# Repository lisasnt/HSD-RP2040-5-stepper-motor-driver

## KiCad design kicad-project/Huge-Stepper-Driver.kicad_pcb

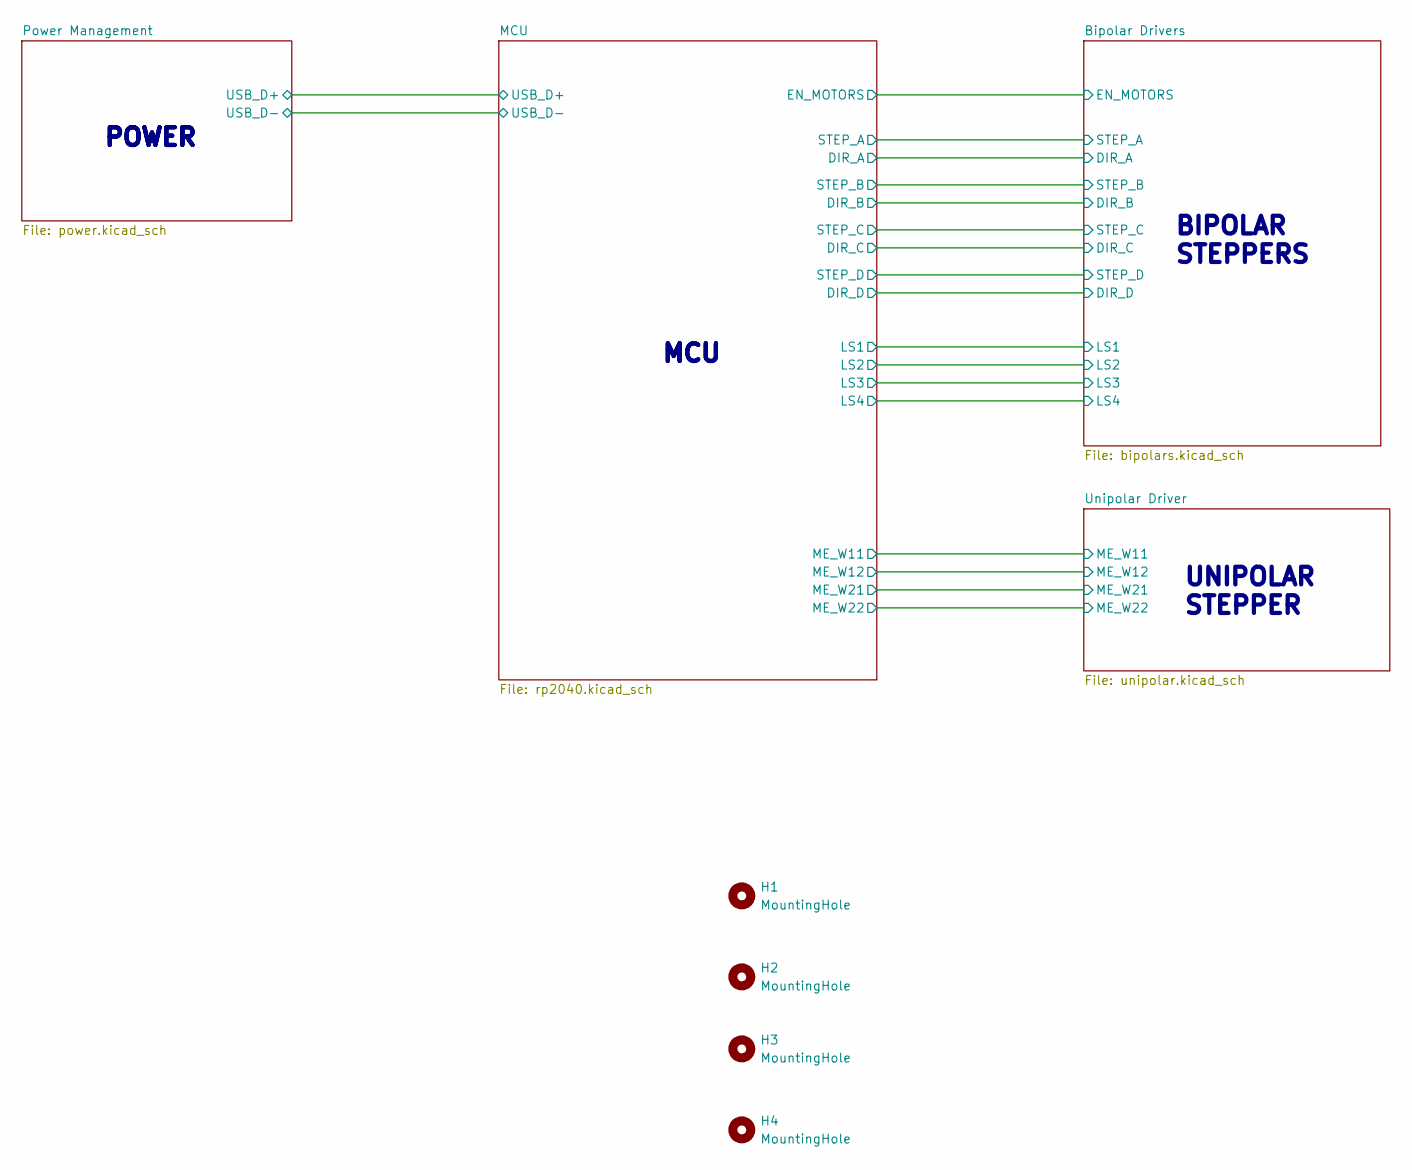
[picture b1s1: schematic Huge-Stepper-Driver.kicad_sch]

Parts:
H1, H2, H3, H4: MountingHole; MountingHole_3.2mm_M3

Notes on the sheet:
MCU
UNIPOLAR STEPPER
POWER
BIPOLAR STEPPERS

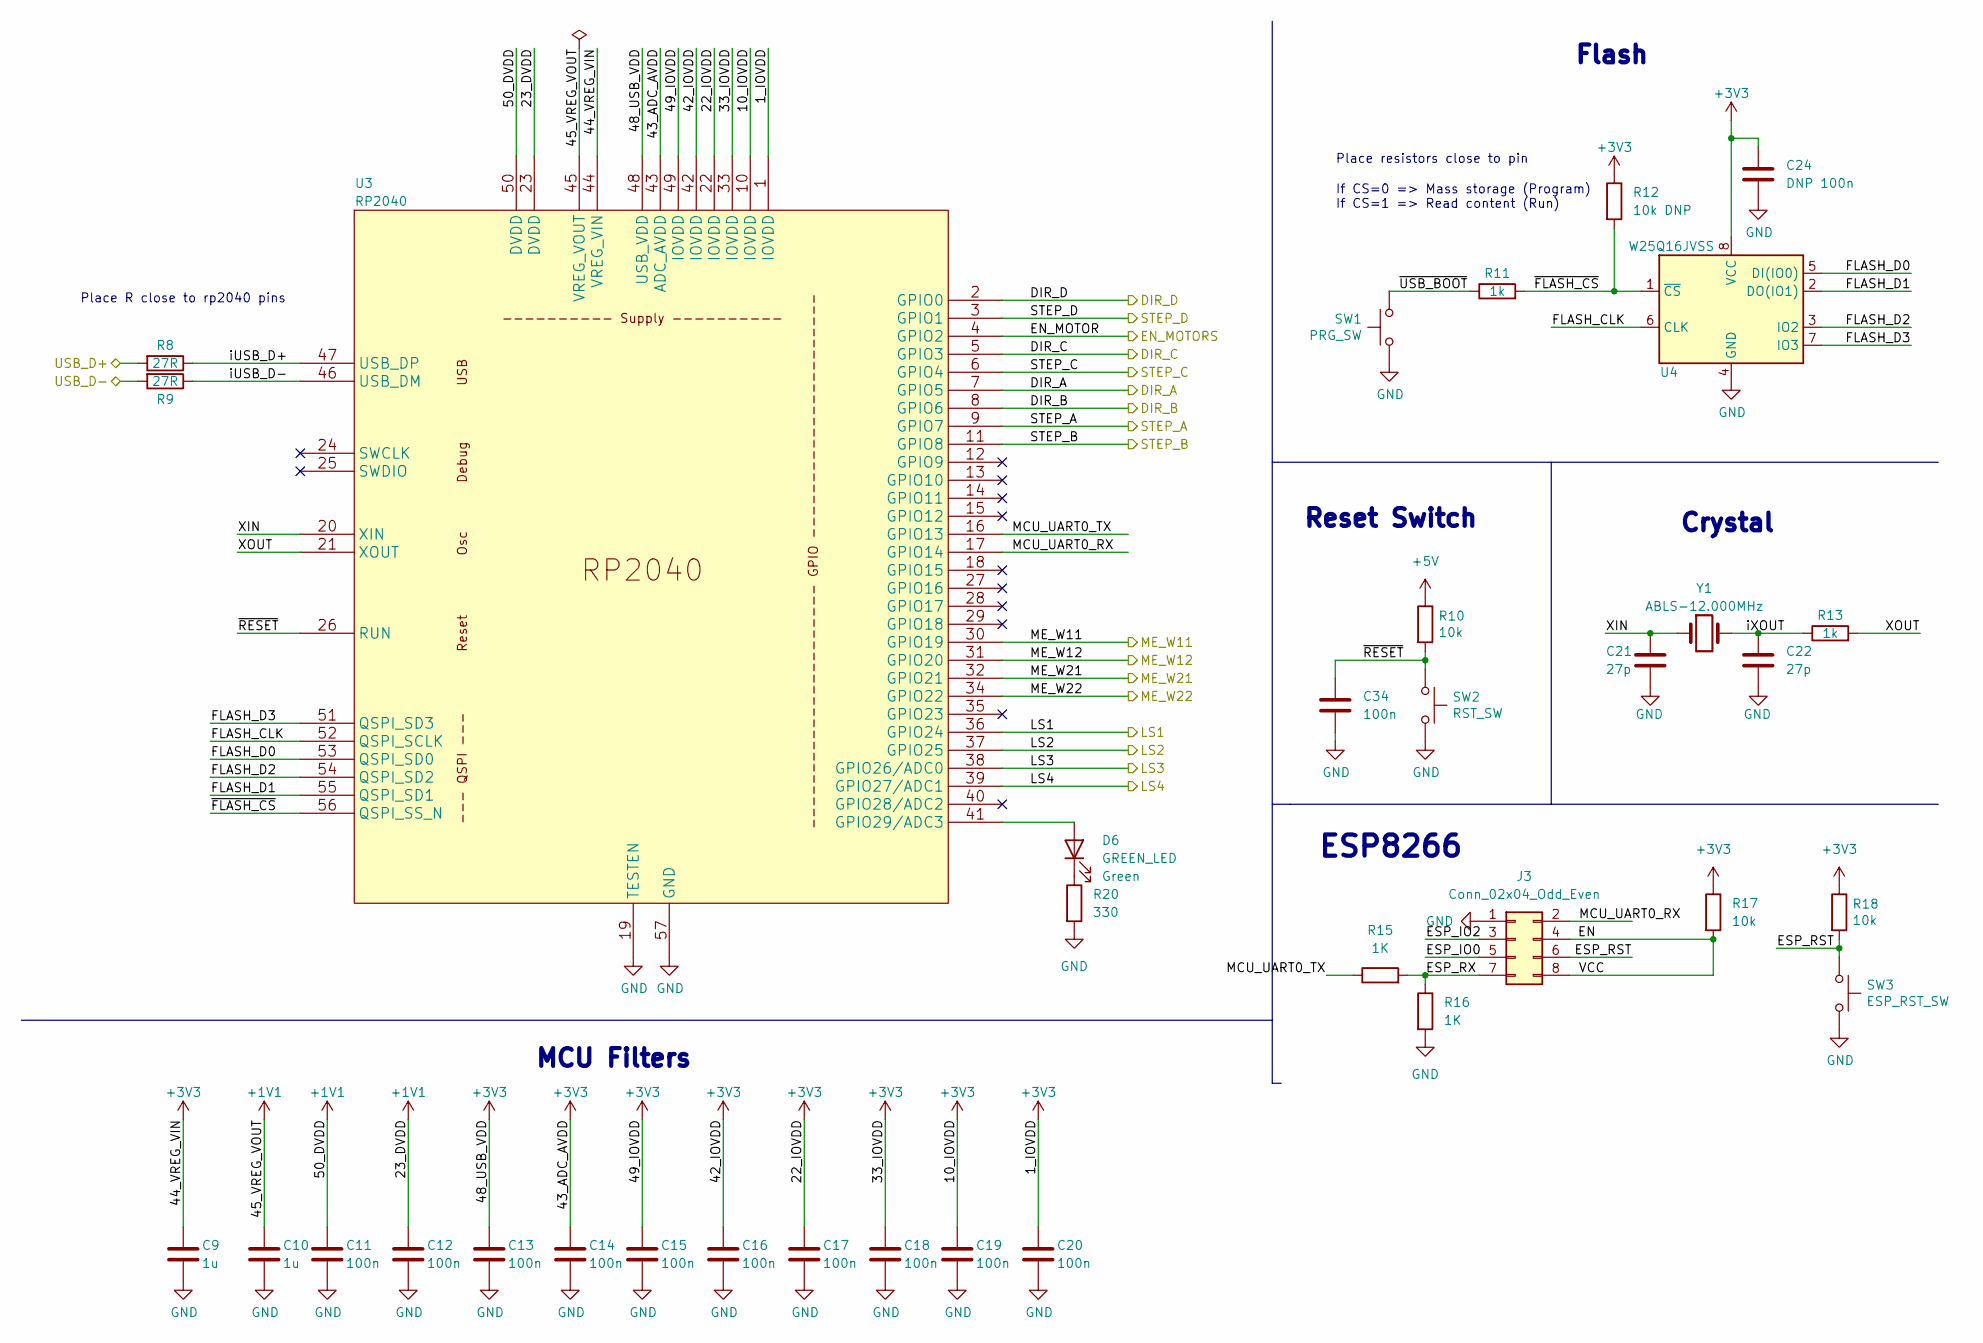
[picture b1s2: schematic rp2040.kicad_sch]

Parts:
C9, C10: 1u; C_0805_2012Metric
C11, C12, C13, C14, C15, C16, C17, C18, C19, C20, C34: 100n; C_0603_1608Metric
C21, C22: 27p; C_0603_1608Metric
C24: DNP 100n; C_0603_1608Metric
D6: GREEN_LED; LED_0603_1608Metric
J3: Conn_02x04_Odd_Even; PinHeader_2x04_P2.54mm_Vertical
R8, R9: 27R; R_0603_1608Metric
R10, R17, R18: 10k; R_0603_1608Metric
R11, R13: 1k; R_0603_1608Metric
R12: 10k DNP; R_0603_1608Metric
R15, R16: 1K; R_0603_1608Metric
R20: 330; R_0603_1608Metric
SW1: PRG_SW; SW_Push_1P1T_NO_CK_KMR2
SW2: RST_SW; SW_Push_1P1T_NO_CK_KMR2
SW3: ESP_RST_SW; SW_Push_1P1T_NO_CK_KMR2
U3: RP2040; RP2040-Hand-Solder
U4: W25Q16JVSS; SOIC-8_5.23x5.23mm_P1.27mm
Y1: ABLS-12.000MHz; Crystal_SMD_HC49-SD

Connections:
+1V1: C10.1, C11.1, C12.1, U3.23 (DVDD), U3.45 (VREG_VOUT), U3.50 (DVDD)
+5V: R10.1; also elsewhere on the board
/Bipolar Drivers/LS1: U3.36 (GPIO24); also elsewhere on the board
/Bipolar Drivers/LS2: U3.37 (GPIO25); also elsewhere on the board
/Bipolar Drivers/LS3: U3.38 (GPIO26/ADC0); also elsewhere on the board
/Bipolar Drivers/LS4: U3.39 (GPIO27/ADC1); also elsewhere on the board
/MCU/DIR_A: U3.7 (GPIO5); also elsewhere on the board
/MCU/DIR_B: U3.8 (GPIO6); also elsewhere on the board
/MCU/DIR_C: U3.5 (GPIO3); also elsewhere on the board
/MCU/DIR_D: U3.2 (GPIO0); also elsewhere on the board
/MCU/EN: J3.4, J3.8, R17.2
/MCU/EN_MOTOR: U3.4 (GPIO2); also elsewhere on the board
/MCU/ESP_IO0: J3.5
/MCU/ESP_IO2: J3.3
/MCU/ESP_RST: J3.6, R18.2, SW3.1
/MCU/ESP_RX: J3.7, R15.2, R16.1
/MCU/FLASH_CLK: U3.52 (QSPI_SCLK), U4.6 (CLK)
/MCU/FLASH_D0: U3.53 (QSPI_SD0), U4.5 (DI(IO0))
/MCU/FLASH_D1: U3.55 (QSPI_SD1), U4.2 (DO(IO1))
/MCU/FLASH_D2: U3.54 (QSPI_SD2), U4.3 (IO2)
/MCU/FLASH_D3: U3.51 (QSPI_SD3), U4.7 (IO3)
/MCU/MCU_UART0_RX: J3.2, U3.17 (GPIO14)
/MCU/MCU_UART0_TX: R15.1, U3.16 (GPIO13)
/MCU/ME_W11: U3.30 (GPIO19); also elsewhere on the board
/MCU/ME_W12: U3.31 (GPIO20); also elsewhere on the board
/MCU/ME_W21: U3.32 (GPIO21); also elsewhere on the board
/MCU/ME_W22: U3.34 (GPIO22); also elsewhere on the board
/MCU/STEP_A: U3.9 (GPIO7); also elsewhere on the board
/MCU/STEP_B: U3.11 (GPIO8); also elsewhere on the board
/MCU/STEP_C: U3.6 (GPIO4); also elsewhere on the board
/MCU/STEP_D: U3.3 (GPIO1); also elsewhere on the board
/MCU/USB_D+: R8.2; also elsewhere on the board
/MCU/USB_D-: R9.2; also elsewhere on the board
/MCU/XIN: C21.1, U3.20 (XIN), Y1.1
/MCU/XOUT: R13.2, U3.21 (XOUT)
/MCU/iUSB_D+: R8.1, U3.47 (USB_DP)
/MCU/iUSB_D-: R9.1, U3.46 (USB_DM)
/MCU/iXOUT: C22.1, R13.1, Y1.2
/MCU/~FLASH_CS: R11.2, R12.2, U3.56 (QSPI_SS_N), U4.1 (~CS)
/MCU/~RESET: C34.1, R10.2, SW2.1, U3.26 (RUN)
/MCU/~USB_BOOT: R11.1, SW1.1
GND: C9.2, C10.2, C11.2, C12.2, C13.2, C14.2, C15.2, C16.2, C17.2, C18.2, C19.2, C20.2, C21.2, C22.2, C24.2, C34.2, J3.1, R16.2, R20.2, SW1.2, SW2.2, SW3.2, U3.19 (TESTEN), U3.57 (GND), U4.4 (GND); also elsewhere on the board
unnamed: D6.1 (K), R20.1
unnamed: D6.2 (A), U3.41 (GPIO29/ADC3)

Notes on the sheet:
Reset Switch
Crystal
ESP8266
Flash
If CS=0 => Mass storage (Program) If CS=1 => Read content (Run)
Place resistors close to pin
MCU Filters
Place R close to rp2040 pins

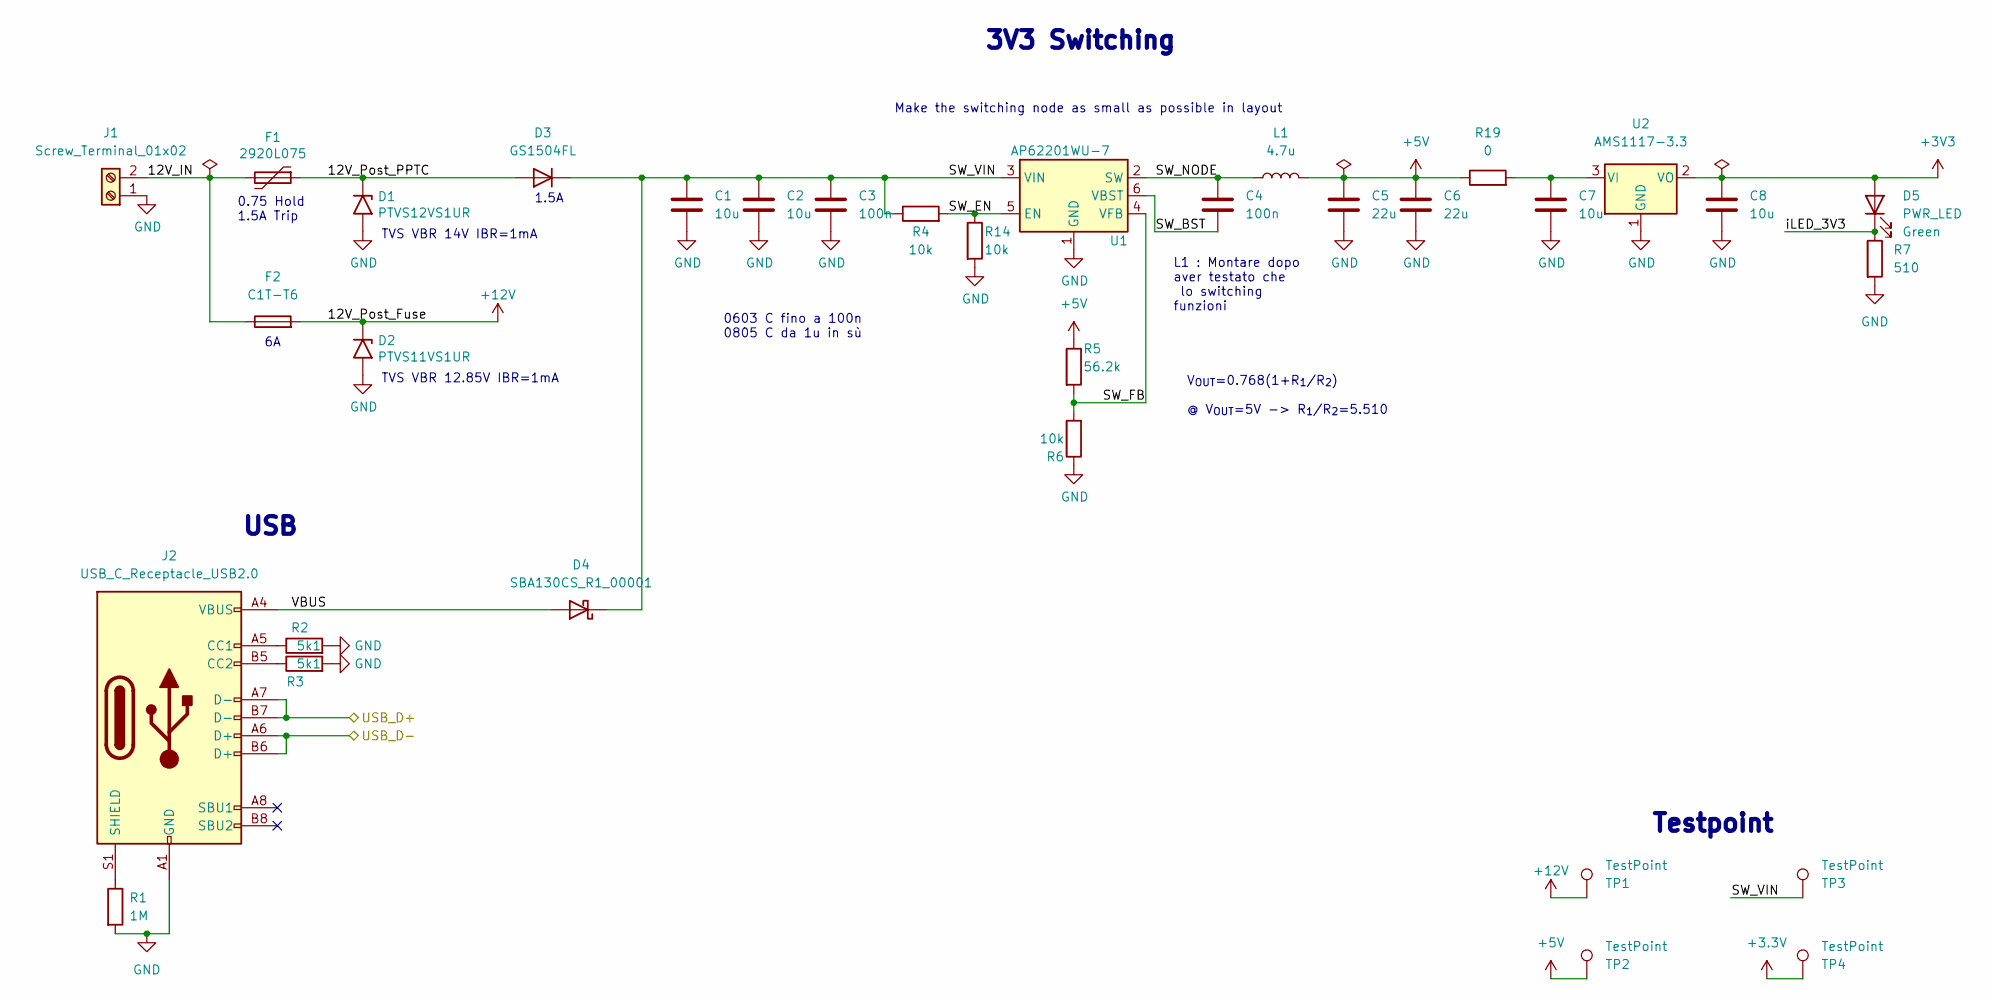
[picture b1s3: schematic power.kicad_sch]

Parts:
C1, C2, C7, C8: 10u; C_0805_2012Metric
C3, C4: 100n; C_0603_1608Metric
C5, C6: 22u; C_0805_2012Metric
D1: PTVS12VS1UR; D_SOD-123
D2: PTVS11VS1UR; D_SOD-123
D3: GS1504FL; D_SOD-123F
D4: SBA130CS_R1_00001; D_SOD-323
D5: PWR_LED; LED_0603_1608Metric
F1: 2920L075; Fuse_2920_7451Metric
F2: C1T-T6; Fuse_1206_3216Metric
J1: Screw_Terminal_01x02; TerminalBlock_RND_205-00001_1x02_P5.00mm_Horizontal
J2: USB_C_Receptacle_USB2.0; USB-C-USB4105-GF-A-120
L1: 4.7u; Inductance
R1: 1M; R_0603_1608Metric
R2, R3: 5k1; R_0603_1608Metric
R4, R6, R14: 10k; R_0603_1608Metric
R5: 56.2k; R_0603_1608Metric
R7: 510; R_0603_1608Metric
R19: 0; R_0603_1608Metric
TP1, TP2, TP3, TP4: TestPoint; TestPoint_Keystone_5005-5009_Compact
U1: AP62201WU-7; TSOT-23-6
U2: AMS1117-3.3; SOT-223-3_TabPin2

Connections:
+5V: C5.1, C6.1, L1.2, R5.1, R19.1, TP2.1; also elsewhere on the board
+12V: D2.1 (A1), F2.2, TP1.1; also elsewhere on the board
/MCU/USB_D+: J2.A7 (D-), J2.B7 (D-); also elsewhere on the board
/MCU/USB_D-: J2.A6 (D+), J2.B6 (D+); also elsewhere on the board
/Power Management/12V_IN: F1.2, F2.1, J1.2
/Power Management/12V_Post_PPTC: D1.1 (A1), D3.2 (A), F1.1
/Power Management/SW_BST: C4.2, U1.6 (VBST)
/Power Management/SW_EN: R4.2, R14.1, U1.5 (EN)
/Power Management/SW_FB: R5.2, R6.2, U1.4 (VFB)
/Power Management/SW_NODE: C4.1, L1.1, U1.2 (SW)
/Power Management/SW_VIN: C1.1, C2.1, C3.1, D3.1 (K), D4.1 (K), R4.1, TP3.1, U1.3 (VIN)
/Power Management/VBUS: D4.2 (A), J2.A4 (VBUS), J2.A9 (VBUS), J2.B4 (VBUS), J2.B9 (VBUS)
/Power Management/iLED_3V3: D5.1 (K), R7.1
GND: C1.2, C2.2, C3.2, C5.2, C6.2, C7.2, C8.2, D1.2 (A2), D2.2 (A2), J1.1, J2.A1 (GND), J2.A12 (GND), J2.B1 (GND), J2.B12 (GND), R1.2, R2.2, R3.2, R6.1, R7.2, R14.2, U1.1 (GND), U2.1 (GND); also elsewhere on the board
unnamed: C7.1, R19.2, U2.3 (VI)
unnamed: J2.A5 (CC1), R2.1
unnamed: J2.B5 (CC2), R3.1
unnamed: J2.S1 (SHIELD), R1.1

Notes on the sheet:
L1 : Montare dopo aver testato che lo switching funzioni
TVS VBR 14V IBR=1mA
Make the switching node as small as possible in layout
Testpoint
0603 C fino a 100n 0805 C da 1u in sù
1.5A
V_{OUT}=0.768(1+R_{1}/R_{2}) @ V_{OUT}=5V -> R_{1}/R_{2}=5.510
0.75 Hold 1.5A Trip
USB
TVS VBR 12.85V IBR=1mA
3V3 Switching

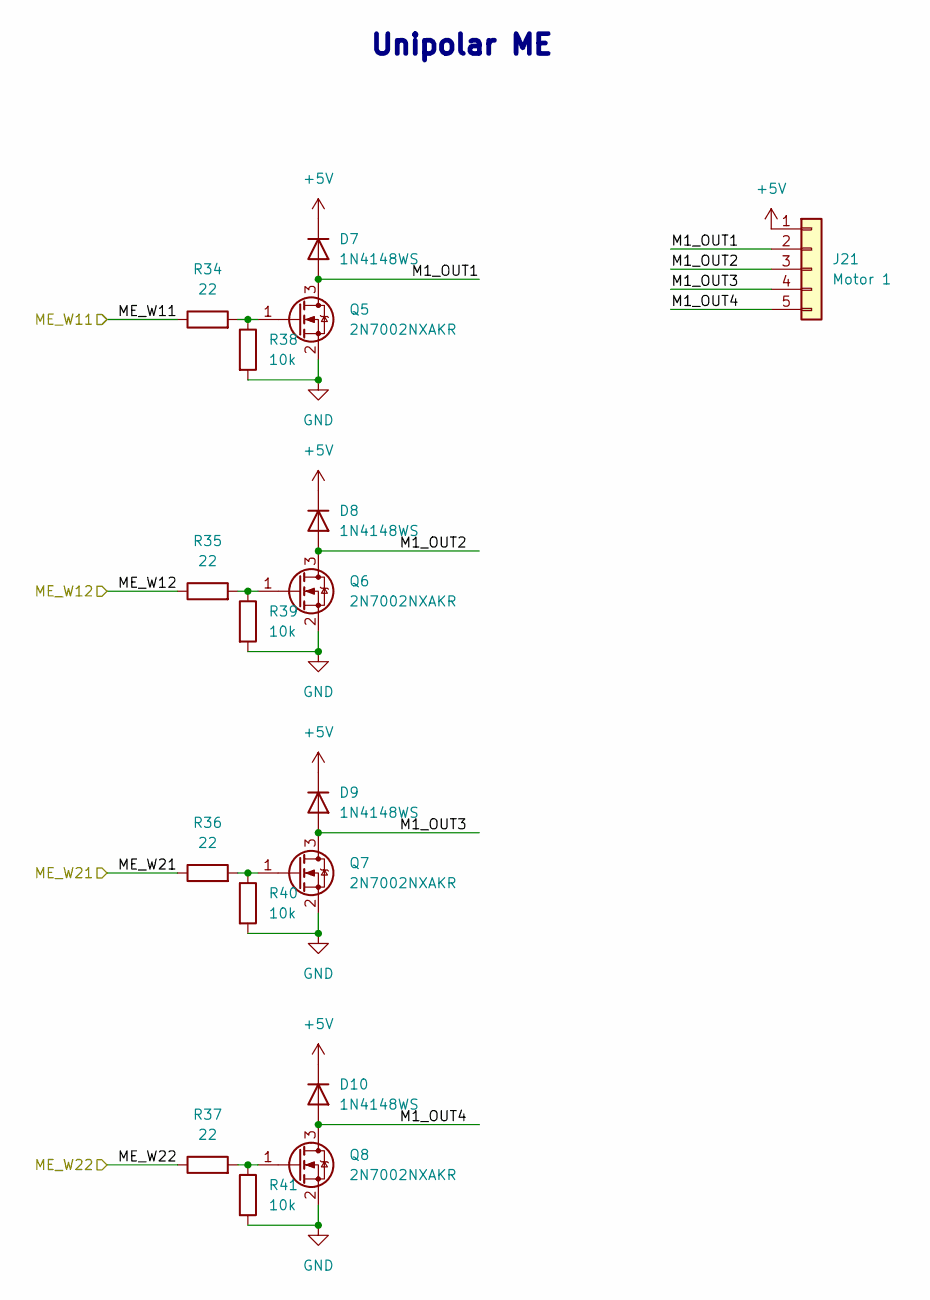
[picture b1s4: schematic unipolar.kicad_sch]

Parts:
D7, D8, D9, D10: 1N4148WS; D_SOD-323
J21: Motor 1; JST_XH_B5B-XH-AM_1x05_P2.50mm_Vertical
Q5, Q6, Q7, Q8: 2N7002NXAKR; SOT-23
R34, R35, R36, R37: 22; R_0603_1608Metric
R38, R39, R40, R41: 10k; R_0603_1608Metric

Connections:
+5V: D7.1 (K), D8.1 (K), D9.1 (K), D10.1 (K), J21.1; also elsewhere on the board
/MCU/ME_W11: R34.1; also elsewhere on the board
/MCU/ME_W12: R35.1; also elsewhere on the board
/MCU/ME_W21: R36.1; also elsewhere on the board
/MCU/ME_W22: R37.1; also elsewhere on the board
/Unipolar Driver /M1_OUT1: D7.2 (A), J21.2, Q5.3 (D)
/Unipolar Driver /M1_OUT2: D8.2 (A), J21.3, Q6.3 (D)
/Unipolar Driver /M1_OUT3: D9.2 (A), J21.4, Q7.3 (D)
/Unipolar Driver /M1_OUT4: D10.2 (A), J21.5, Q8.3 (D)
GND: Q5.2 (S), Q6.2 (S), Q7.2 (S), Q8.2 (S), R38.2, R39.2, R40.2, R41.2; also elsewhere on the board
unnamed: Q5.1 (G), R34.2, R38.1
unnamed: Q6.1 (G), R35.2, R39.1
unnamed: Q7.1 (G), R36.2, R40.1
unnamed: Q8.1 (G), R37.2, R41.1

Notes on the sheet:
Unipolar ME

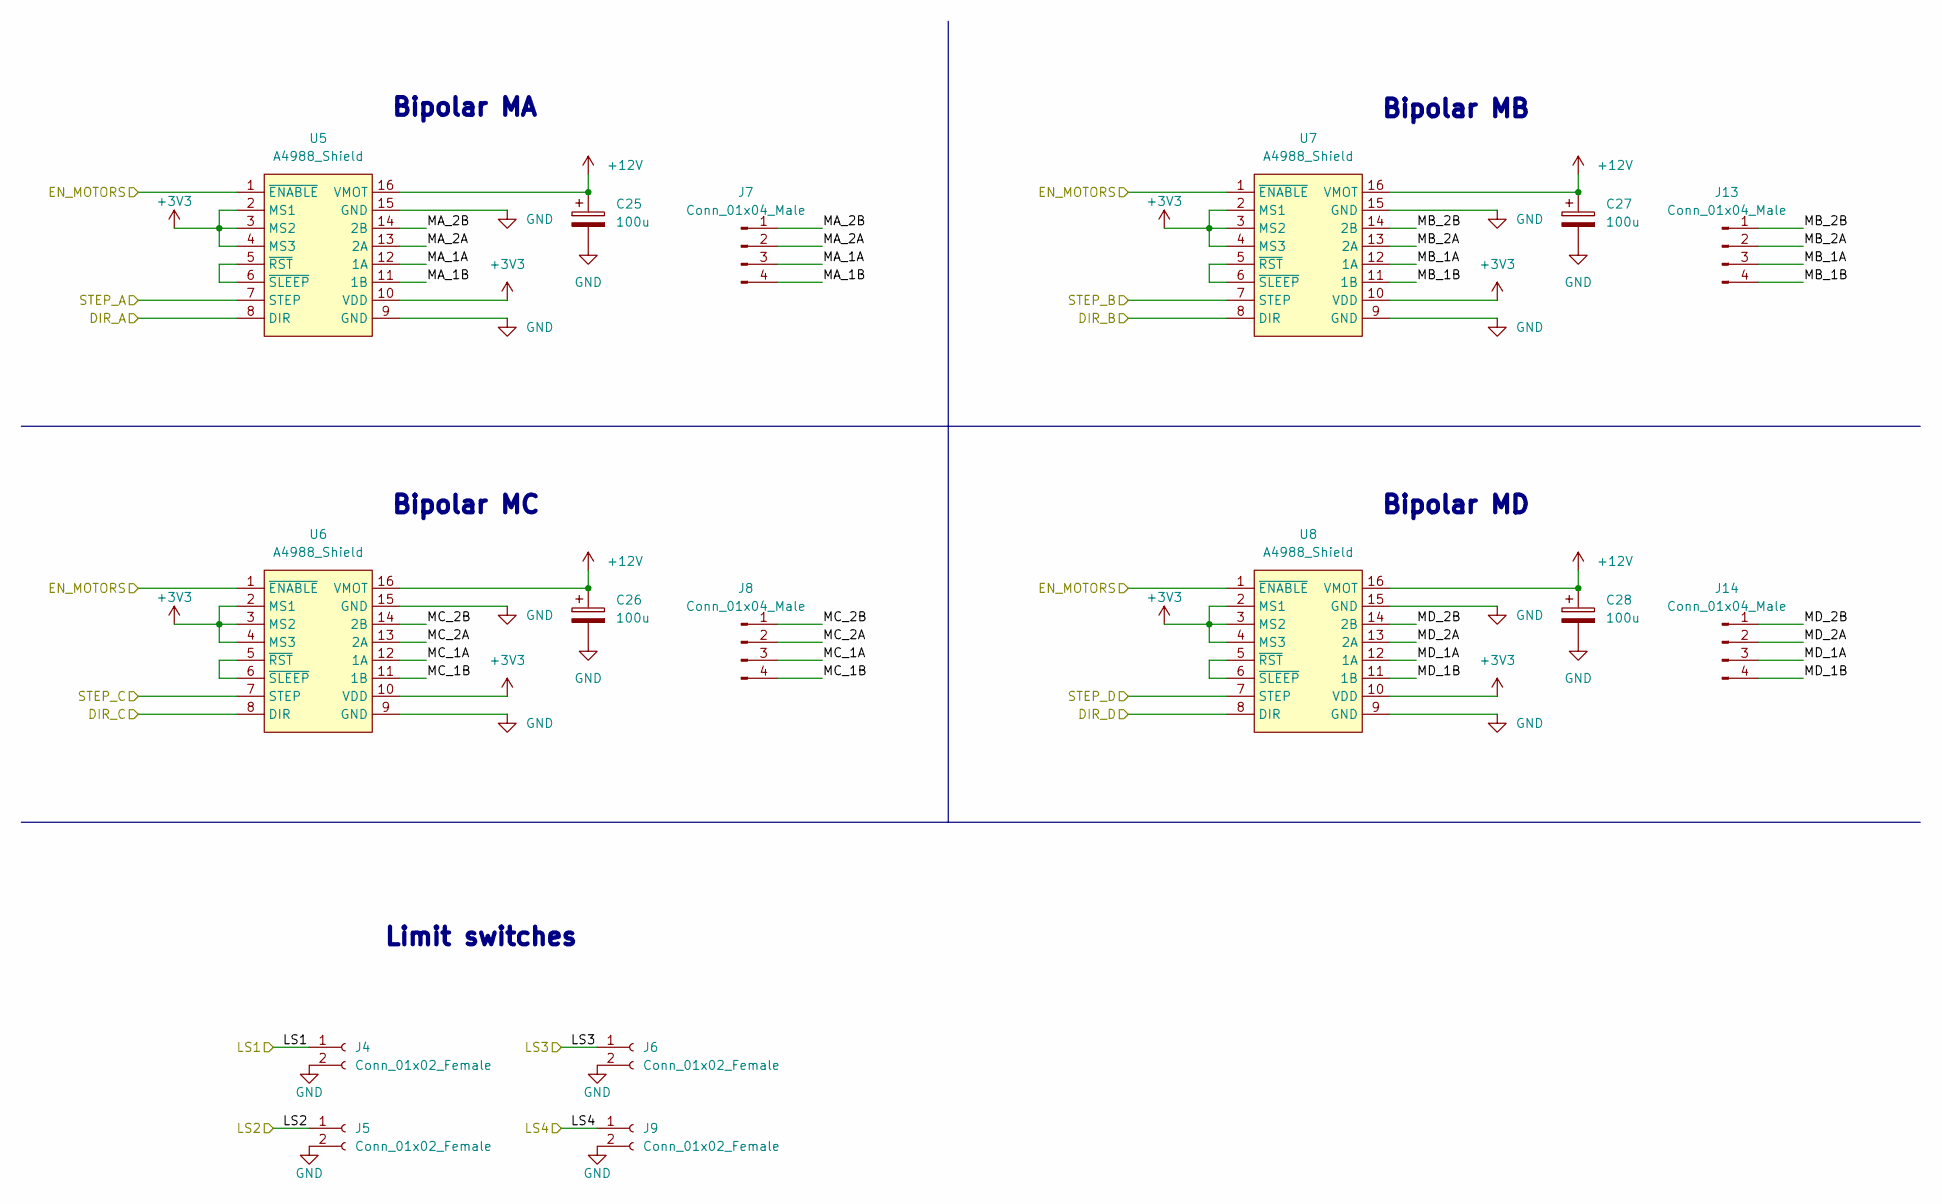
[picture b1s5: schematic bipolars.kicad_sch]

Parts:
C25, C26, C27, C28: 100u; CP_Elec_6.3x5.3
J4, J5, J6, J9: Conn_01x02_Female; PinHeader_1x02_P2.54mm_Vertical
J7, J8, J13, J14: Conn_01x04_Male; PinHeader_1x04_P2.54mm_Vertical
U5, U6, U7, U8: A4988_Shield

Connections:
+12V: C25.1, C26.1, C27.1, C28.1, U5.16 (VMOT), U6.16 (VMOT), U7.16 (VMOT), U8.16 (VMOT); also elsewhere on the board
/Bipolar Drivers/LS1: J4.1; also elsewhere on the board
/Bipolar Drivers/LS2: J5.1; also elsewhere on the board
/Bipolar Drivers/LS3: J6.1; also elsewhere on the board
/Bipolar Drivers/LS4: J9.1; also elsewhere on the board
/Bipolar Drivers/MA_1A: J7.3, U5.12 (1A)
/Bipolar Drivers/MA_1B: J7.4, U5.11 (1B)
/Bipolar Drivers/MA_2A: J7.2, U5.13 (2A)
/Bipolar Drivers/MA_2B: J7.1, U5.14 (2B)
/Bipolar Drivers/MB_1A: J13.3, U7.12 (1A)
/Bipolar Drivers/MB_1B: J13.4, U7.11 (1B)
/Bipolar Drivers/MB_2A: J13.2, U7.13 (2A)
/Bipolar Drivers/MB_2B: J13.1, U7.14 (2B)
/Bipolar Drivers/MC_1A: J8.3, U6.12 (1A)
/Bipolar Drivers/MC_1B: J8.4, U6.11 (1B)
/Bipolar Drivers/MC_2A: J8.2, U6.13 (2A)
/Bipolar Drivers/MC_2B: J8.1, U6.14 (2B)
/Bipolar Drivers/MD_1A: J14.3, U8.12 (1A)
/Bipolar Drivers/MD_1B: J14.4, U8.11 (1B)
/Bipolar Drivers/MD_2A: J14.2, U8.13 (2A)
/Bipolar Drivers/MD_2B: J14.1, U8.14 (2B)
/MCU/DIR_A: U5.8 (DIR); also elsewhere on the board
/MCU/DIR_B: U7.8 (DIR); also elsewhere on the board
/MCU/DIR_C: U6.8 (DIR); also elsewhere on the board
/MCU/DIR_D: U8.8 (DIR); also elsewhere on the board
/MCU/EN_MOTOR: U5.1 (~ENABLE), U6.1 (~ENABLE), U7.1 (~ENABLE), U8.1 (~ENABLE); also elsewhere on the board
/MCU/STEP_A: U5.7 (STEP); also elsewhere on the board
/MCU/STEP_B: U7.7 (STEP); also elsewhere on the board
/MCU/STEP_C: U6.7 (STEP); also elsewhere on the board
/MCU/STEP_D: U8.7 (STEP); also elsewhere on the board
GND: C25.2, C26.2, C27.2, C28.2, J4.2, J5.2, J6.2, J9.2, U5.9 (GND), U5.15 (GND), U6.9 (GND), U6.15 (GND), U7.9 (GND), U7.15 (GND), U8.9 (GND), U8.15 (GND); also elsewhere on the board
unnamed: U5.5 (~RST), U5.6 (~SLEEP)
unnamed: U6.5 (~RST), U6.6 (~SLEEP)
unnamed: U7.5 (~RST), U7.6 (~SLEEP)
unnamed: U8.5 (~RST), U8.6 (~SLEEP)

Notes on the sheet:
Bipolar MB
Bipolar MC
Limit switches
Bipolar MD
Bipolar MA

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
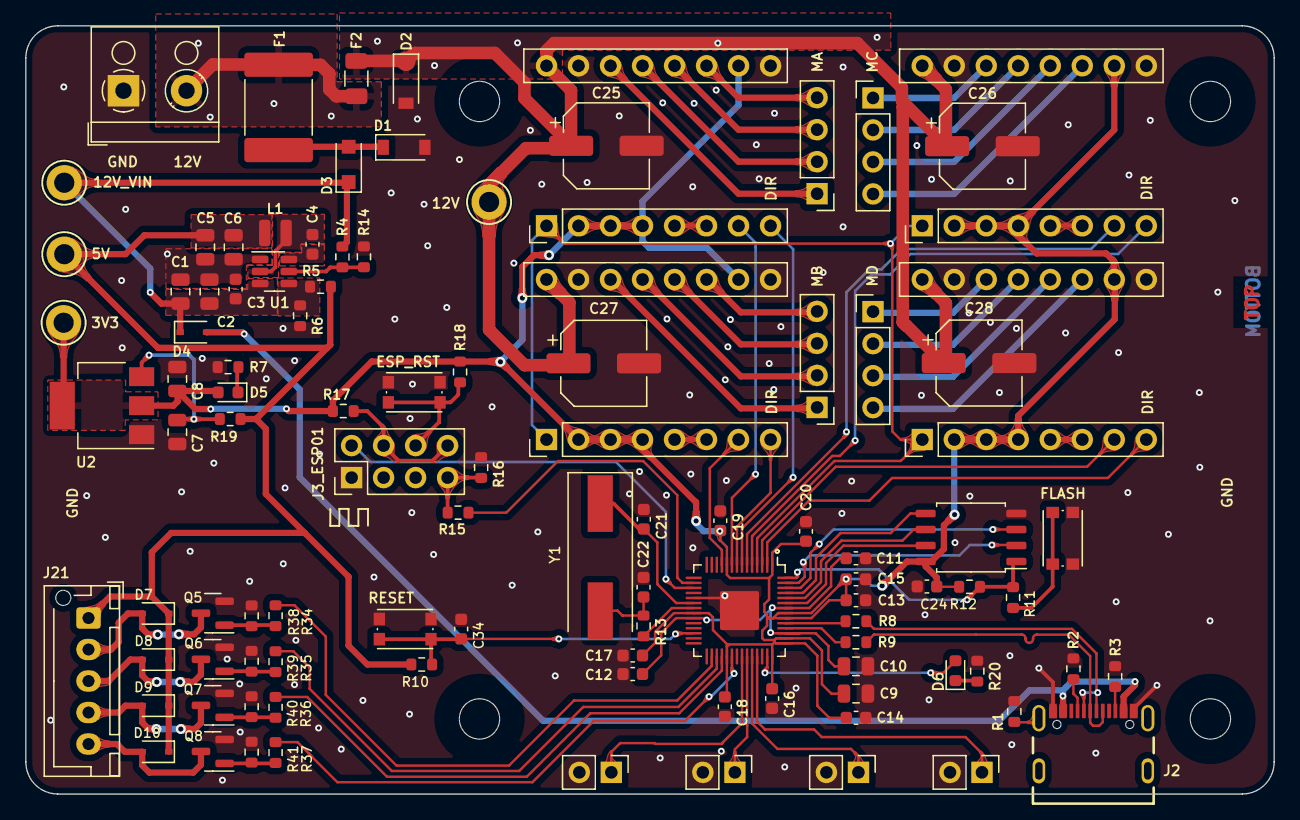
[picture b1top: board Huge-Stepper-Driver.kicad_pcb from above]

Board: 2 copper layers, 99.1 x 61.0 mm, 105 parts (0 on the bottom side), 85 nets.

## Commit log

2022-04-04 update to step 8
2022-04-12 hw: rename poject and create project library
2022-04-12 hw: add power managment
2022-04-13 readme update
2022-04-14 doc: two datasheet added
2022-04-21 hw: update
2022-05-01 hw: add esp8266
2022-05-01 hw: change to rp2040
2022-05-01 hw: change power management and drivers
2022-05-04 Bipolar pins
2022-05-05 hw: update to complete schematic
2022-05-07 hw: finish schematic
2022-05-10 hw: finish schematic, PS i2c R_pull-up wrong
2022-05-10 hw: semplified schemtic, removed peripherals, fix merge
2022-05-11 hw: place layout component
2022-05-12 prima versione pcb layout
2022-05-12 settings pcb cambiate
2022-05-13 fix unipolar e qualche rotta
2022-05-16 hw: HSD v1.0 w/out peripherals
2022-05-18 hw: updated HSD v1.0 + add gerber files
2022-05-20 hw: update HSD v1.0
2022-05-21 nuovi gerber e credits
